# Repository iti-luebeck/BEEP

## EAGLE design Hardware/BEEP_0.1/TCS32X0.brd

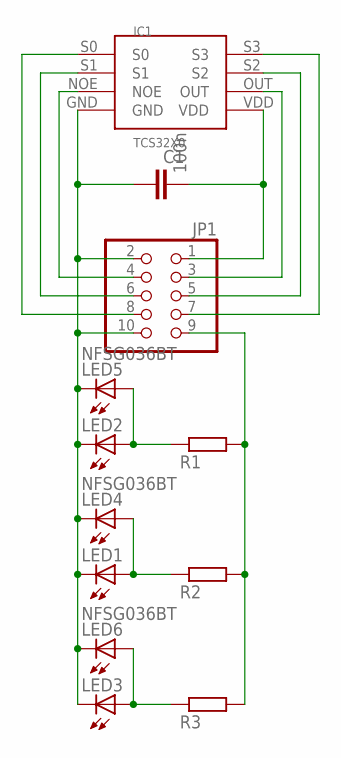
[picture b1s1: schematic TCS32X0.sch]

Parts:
C1: 100n; C0805
IC1: TCS32X0
JP1: PINHD-2X5; 2X05
LED1, LED2, LED3: LED3MM
LED4, LED5, LED6: NFSG036BT
R1, R2, R3: R-EU_M0805; M0805

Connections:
GND: C1.1, IC1.GND, JP1.2, JP1.10, LED1.K (C), LED2.K (C), LED3.K (C), LED4.C, LED5.C, LED6.C
unnamed: JP1.9, R1.2, R2.2, R3.2
unnamed: IC1.NOE, JP1.4
unnamed: IC1.S1, JP1.6
unnamed: C1.2, IC1.VDD, JP1.1
unnamed: IC1.OUT, JP1.3
unnamed: IC1.S2, JP1.5
unnamed: LED2.A, LED5.A, R1.1
unnamed: LED1.A, LED4.A, R2.1
unnamed: LED3.A, LED6.A, R3.1
unnamed: IC1.S0, JP1.8
unnamed: IC1.S3, JP1.7

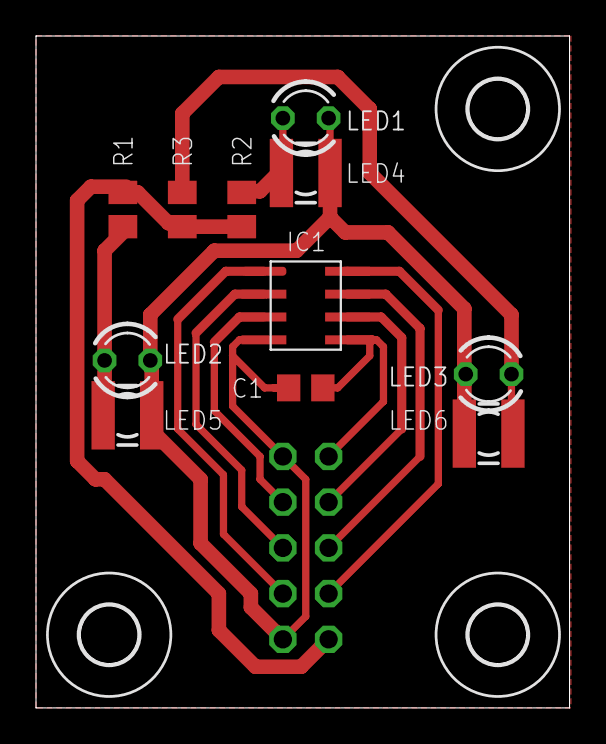
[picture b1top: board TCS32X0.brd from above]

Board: 2 copper layers, 29.6 x 37.3 mm, 15 parts (1 on the bottom side), 12 nets.

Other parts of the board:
U$2, U$3, U$4: 3,2

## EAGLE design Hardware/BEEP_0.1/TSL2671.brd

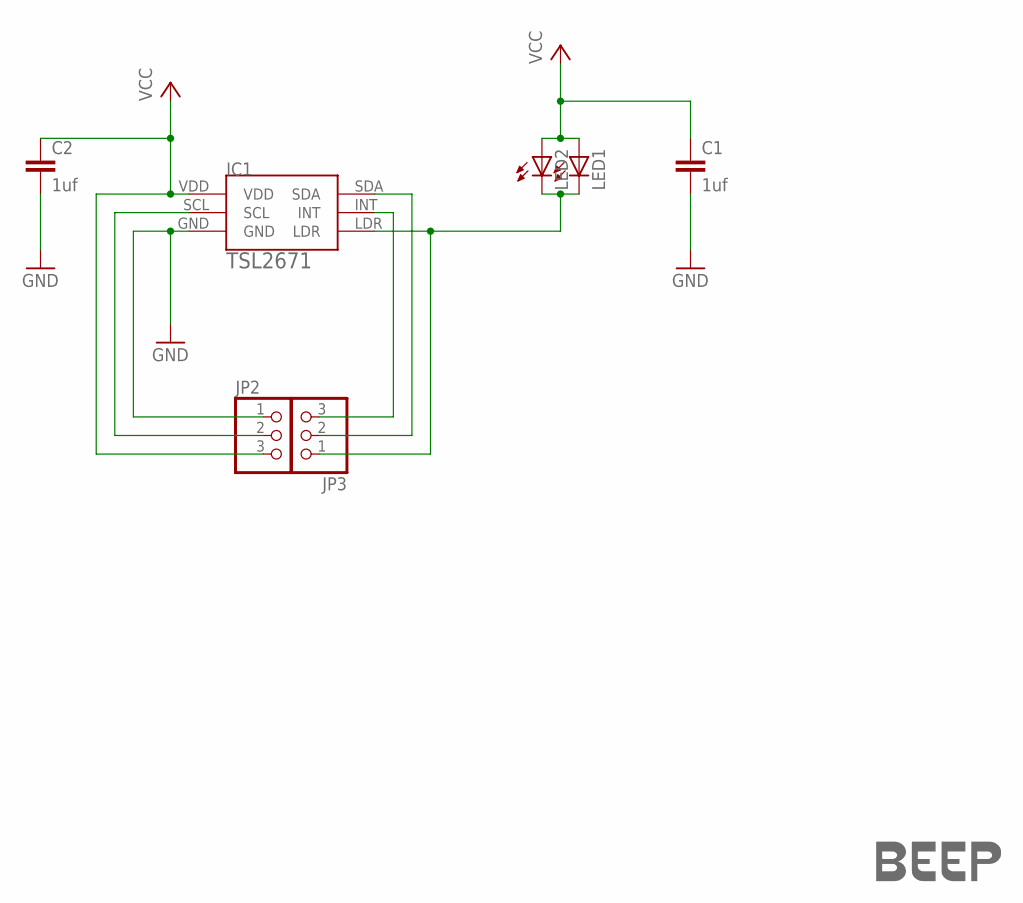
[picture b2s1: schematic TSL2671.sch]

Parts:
C1: 1uf; C025-025X050
C2: 1uf; C0805K
IC1: TSL2671
JP2, JP3: PINHD-1X3; 1X03
LED1: LED5MM
LED2: LEDCHIP-LED0805; CHIP-LED0805
U$1: LOGO-COPPER4; COPPER4

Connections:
GND: C1.2, C2.2, IC1.GND, JP2.1
unnamed: IC1.LDR, JP3.1, LED1.K (C), LED2.C
unnamed: IC1.SCL, JP2.2
unnamed: IC1.SDA, JP3.2
unnamed: IC1.INT, JP3.3
VCC: C1.1, C2.1, IC1.VDD, JP2.3, LED1.A, LED2.A

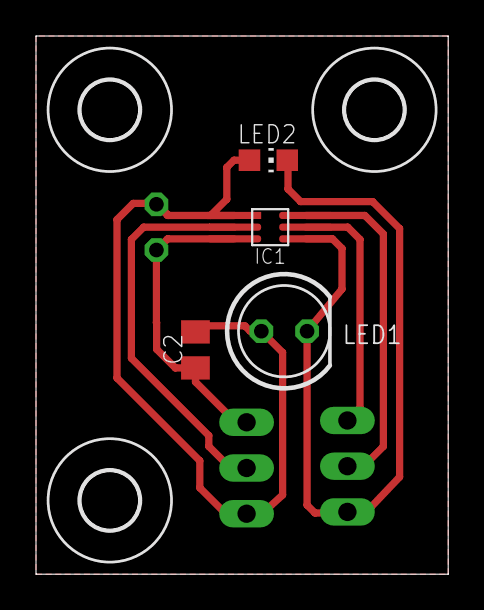
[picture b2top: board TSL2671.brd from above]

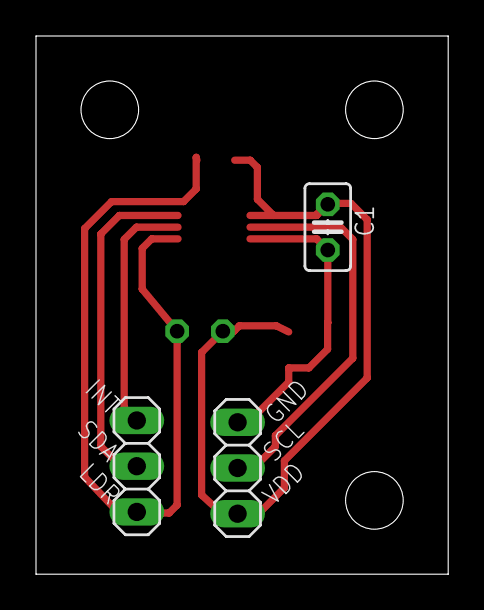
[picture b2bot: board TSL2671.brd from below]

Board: 2 copper layers, 22.9 x 29.9 mm, 11 parts (3 on the bottom side), 6 nets.

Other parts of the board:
U$2, U$3, U$4: 3,2

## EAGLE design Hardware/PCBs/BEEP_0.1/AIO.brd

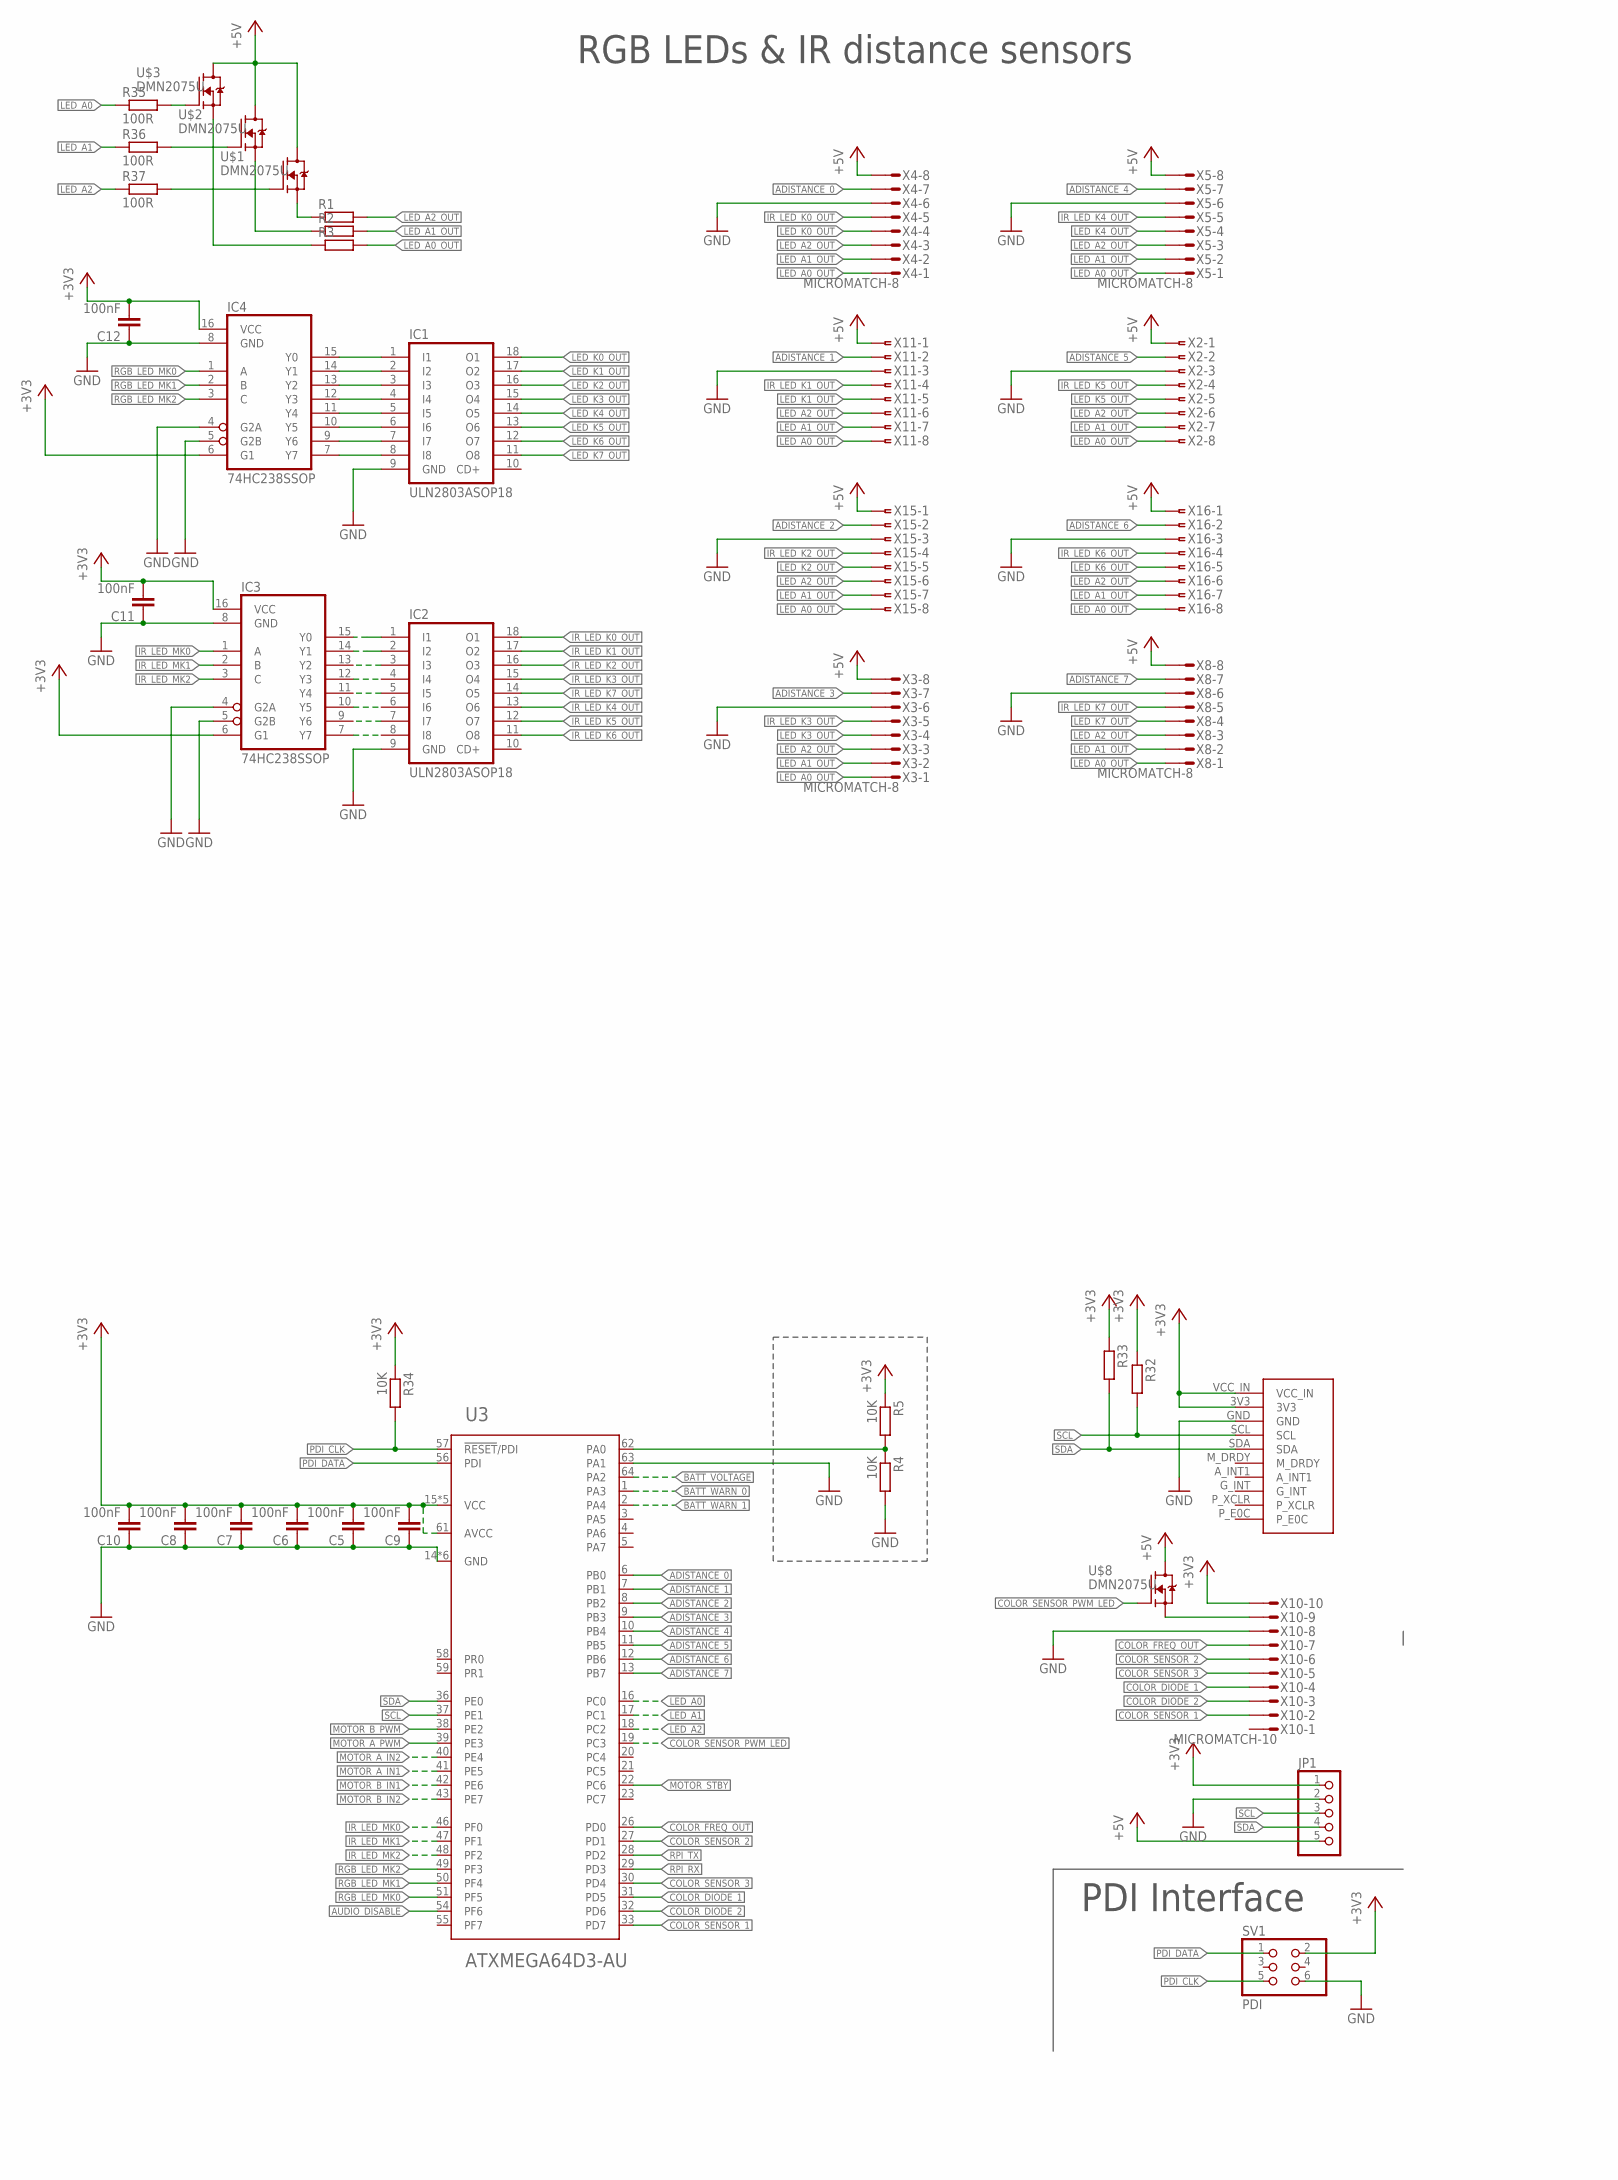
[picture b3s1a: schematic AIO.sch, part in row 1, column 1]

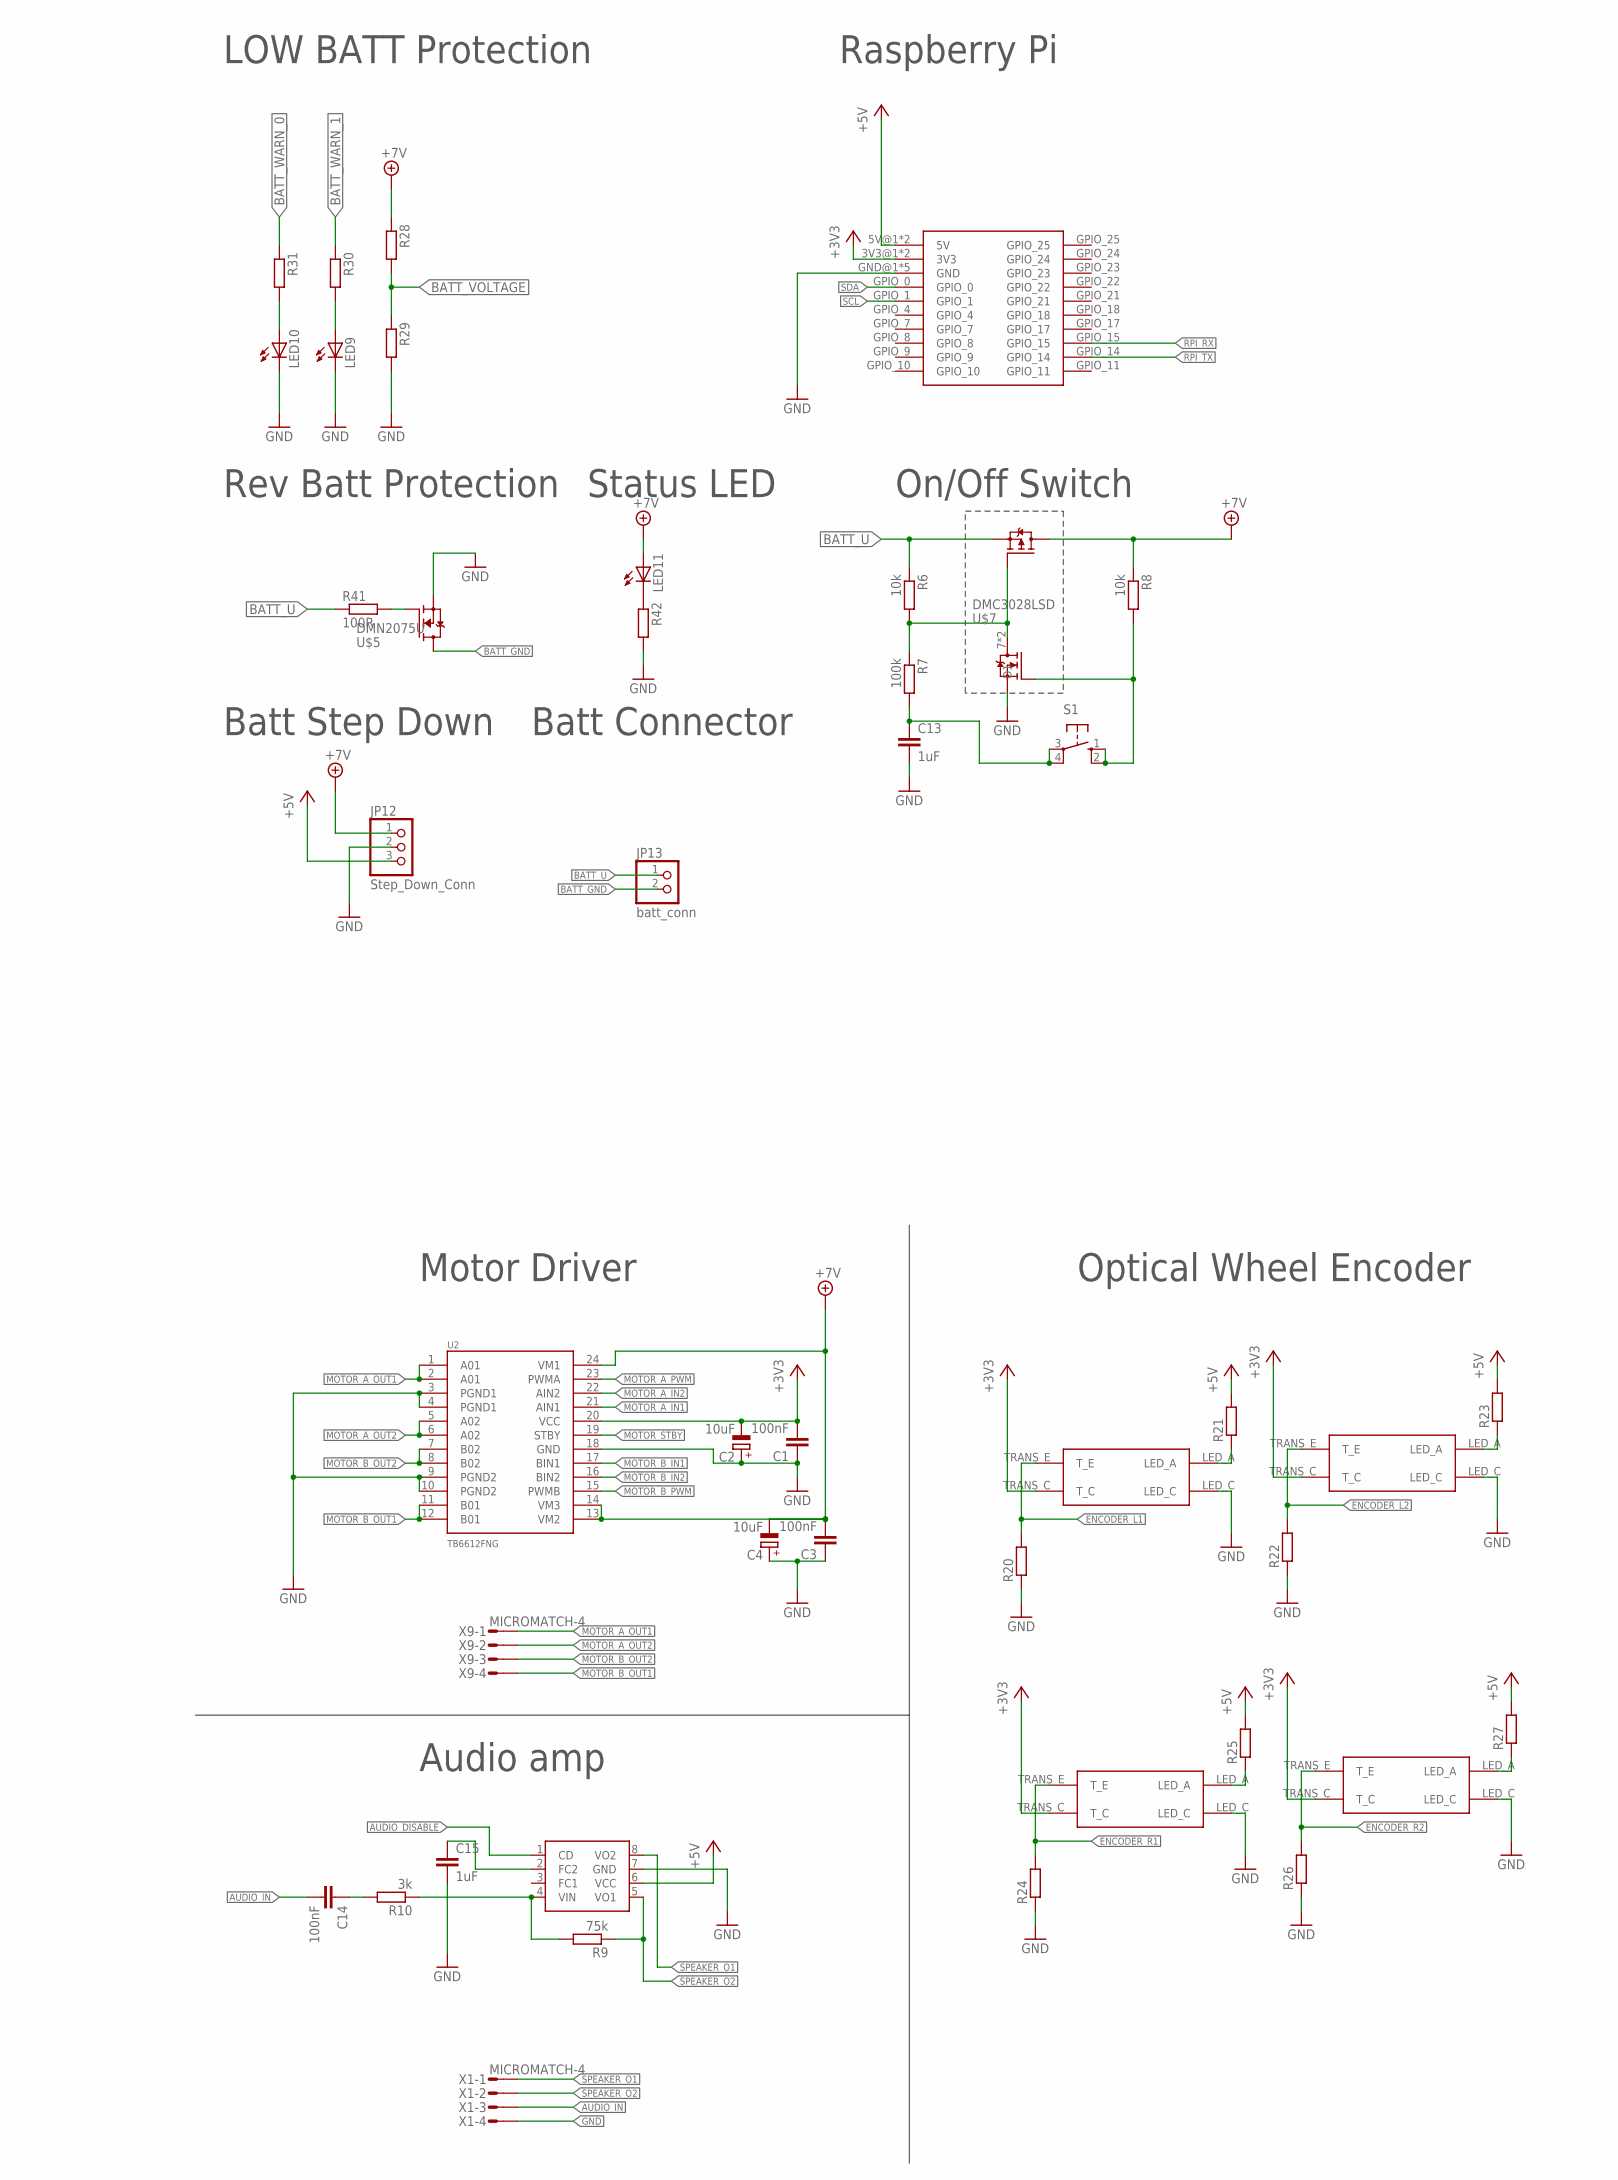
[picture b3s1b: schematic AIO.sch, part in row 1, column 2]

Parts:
C1, C3, C5, C6, C7, C8, C9, C10, C11, C12, C14: 100nF; C0603
C2, C4: 10uF; SMC_D
C13, C15: 1uF; C0603
IC1, IC2: ULN2803ASOP18; SOP18
IC3, IC4: 74HC238SSOP; SSOP16
IC5: TS34119SMD; SO08
JP1: PINHD-1X5; 1X05
JP12: Step_Down_Conn; 1X03
JP13: batt_conn; 1X02
LED9, LED10, LED11: LEDCHIPLED_0603; CHIPLED_0603
R1, R2, R3, R20, R21, R22, R23, R24, R25, R26, R27, R28, R29, R30, R31, R32, R33, R42: R-EU_R0603; R0603
R4, R5, R34: 10K; R0603
R6, R8: 10k; R0603
R7: 100k; R0603
R9: 75k; R0603
R10: 3k; R0603
R35, R36, R37, R41: 100R; R0603
S1: 10-XX; B3F-10XX
SV1: PDI; 2X03
U2: TB6612FNG; SSOP24
U3: ATXMEGA64D3-AU; TQFP-64A-64
U$1, U$2, U$3, U$5, U$8: DMN2075U; SOT95P240X112-3N
U$7: DMC3028LSD; SO08
U$21, U$22, U$23, U$24: CNY70
U$25: GY-81
U$26: RASPBERRY-PI; RASPERRRY-PI
X1, X9: MICROMATCH-4
X2, X11, X15, X16: FSIDE-8
X3, X4, X5, X8: MICROMATCH-8
X10: MICROMATCH-10

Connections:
+3V3: C1.2, C2.-, C5.2, C6.2, C7.2, C8.2, C9.2, C10.2, C11.2, C12.2, IC3.6 (G1), IC3.16 (VCC), IC4.6 (G1), IC4.16 (VCC), JP1.1, R5.1, R32.1, R33.1, R34.1, SV1.2, U2.20 (VCC), U3.15 (VCC), U3.25 (VCC), U3.35 (VCC), U3.45 (VCC), U3.53 (VCC), U3.61 (AVCC), U$21.TRANS_C (T_C), U$22.TRANS_C (T_C), U$23.TRANS_C (T_C), U$24.TRANS_C (T_C), U$25.3V3, U$25.VCC_IN, U$26.3V3@1 (3V3), U$26.3V3@2 (3V3), X10.10
+5V: IC5.6 (VCC), JP1.5, JP12.3, R21.2, R23.2, R25.2, R27.2, U$1.D, U$2.D, U$3.D, U$8.D, U$26.5V@1 (5V), U$26.5V@2 (5V), X2.1, X3.8, X4.8, X5.8, X8.8, X11.1, X15.1, X16.1
+7V: C3.2, C4.-, JP12.1, LED11.A, R8.1, R28.1, U2.13 (VM2), U2.14 (VM3), U2.24 (VM1), U$7.5 (D2), U$7.6 (D2)
ADISTANCE_0: U3.6 (PB0), X4.7
ADISTANCE_1: U3.7 (PB1), X11.2
ADISTANCE_2: U3.8 (PB2), X15.2
ADISTANCE_3: U3.9 (PB3), X3.7
ADISTANCE_4: U3.10 (PB4), X5.7
ADISTANCE_5: U3.11 (PB5), X2.2
ADISTANCE_6: U3.12 (PB6), X16.2
ADISTANCE_7: U3.13 (PB7), X8.7
AUDIO_DISABLE: IC5.1 (CD), U3.54 (PF6)
AUDIO_IN: C14.2, X1.3
BATT_GND: JP13.2, U$5.D
BATT_U: JP13.1, R6.1, R41.1, U$7.3 (S2)
BATT_VOLTAGE: R28.2, R29.1, U3.64 (PA2)
BATT_WARN_0: R31.1, U3.1 (PA3)
BATT_WARN_1: R30.1, U3.2 (PA4)
COLOR_DIODE_1: U3.31 (PD5), X10.4
COLOR_DIODE_2: U3.32 (PD6), X10.3
COLOR_FREQ_OUT: U3.26 (PD0), X10.7
COLOR_SENSOR_1: U3.33 (PD7), X10.2
COLOR_SENSOR_2: U3.27 (PD1), X10.6
COLOR_SENSOR_3: U3.30 (PD4), X10.5
COLOR_SENSOR_PWM_LED: U3.19 (PC3), U$8.G
ENCODER_L1: R20.2, U$21.TRANS_E (T_E)
ENCODER_L2: R22.2, U$22.TRANS_E (T_E)
ENCODER_R1: R24.2, U$23.TRANS_E (T_E)
ENCODER_R2: R26.2, U$24.TRANS_E (T_E)
GND: C1.1, C2.+, C3.1, C4.+, C5.1, C6.1, C7.1, C8.1, C9.1, C10.1, C11.1, C12.1, C13.2, C15.2, IC1.9 (GND), IC2.9 (GND), IC3.4 (G2A), IC3.5 (G2B), IC3.8 (GND), IC4.4 (G2A), IC4.5 (G2B), IC4.8 (GND), IC5.7 (GND), JP1.2, JP12.2, LED9.C, LED10.C, R4.2, R20.1, R22.1, R24.1, R26.1, R29.2, R42.2, SV1.6, U2.3 (PGND1), U2.4 (PGND1), U2.9 (PGND2), U2.10 (PGND2), U2.18 (GND), U3.14 (GND), U3.24 (GND), U3.34 (GND), U3.44 (GND), U3.52 (GND), U3.60 (GND), U3.63 (PA1), U$5.S, U$7.1 (S1), U$21.LED_C, U$22.LED_C, U$23.LED_C, U$24.LED_C, U$25.GND, U$26.GND@1 (GND), U$26.GND@2 (GND), U$26.GND@3 (GND), U$26.GND@4 (GND), U$26.GND@5 (GND), X1.4, X2.3, X3.6, X4.6, X5.6, X8.6, X10.8, X11.3, X15.3, X16.3
IR_LED_K0: IC2.1 (I1), IC3.15 (Y0)
IR_LED_K0_OUT: IC2.18 (O1), X4.5
IR_LED_K1: IC2.2 (I2), IC3.14 (Y1)
IR_LED_K1_OUT: IC2.17 (O2), X11.4
IR_LED_K2_OUT: IC2.16 (O3), X15.4
IR_LED_K3_OUT: IC2.15 (O4), X3.5
IR_LED_K4_OUT: IC2.13 (O6), X5.5
IR_LED_K5_OUT: IC2.12 (O7), X2.4
IR_LED_K6_OUT: IC2.11 (O8), X16.4
IR_LED_K7_OUT: IC2.14 (O5), X8.5
IR_LED_MK0: IC3.1 (A), U3.46 (PF0)
IR_LED_MK1: IC3.2 (B), U3.47 (PF1)
IR_LED_MK2: IC3.3 (C), U3.48 (PF2)
LED_A0: R35.1, U3.16 (PC0)
LED_A0_OUT: R3.2, X2.8, X3.1, X4.1, X5.1, X8.1, X11.8, X15.8, X16.8
LED_A1: R36.1, U3.17 (PC1)
LED_A1_OUT: R2.2, X2.7, X3.2, X4.2, X5.2, X8.2, X11.7, X15.7, X16.7
LED_A2: R37.1, U3.18 (PC2)
LED_A2_OUT: R1.2, X2.6, X3.3, X4.3, X5.3, X8.3, X11.6, X15.6, X16.6
LED_K0_OUT: IC1.18 (O1), X4.4
LED_K1_OUT: IC1.17 (O2), X11.5
LED_K2_OUT: IC1.16 (O3), X15.5
LED_K3_OUT: IC1.15 (O4), X3.4
LED_K4_OUT: IC1.14 (O5), X5.4
LED_K5_OUT: IC1.13 (O6), X2.5
LED_K6_OUT: IC1.12 (O7), X16.5
LED_K7_OUT: IC1.11 (O8), X8.4
MOTOR_A_IN1: U2.21 (AIN1), U3.41 (PE5)
MOTOR_A_IN2: U2.22 (AIN2), U3.40 (PE4)
MOTOR_A_OUT1: U2.1 (A01), U2.2 (A01), X9.1
MOTOR_A_OUT2: U2.5 (A02), U2.6 (A02), X9.2
MOTOR_A_PWM: U2.23 (PWMA), U3.39 (PE3)
MOTOR_B_IN1: U2.17 (BIN1), U3.42 (PE6)
MOTOR_B_IN2: U2.16 (BIN2), U3.43 (PE7)
MOTOR_B_OUT1: U2.11 (B01), U2.12 (B01), X9.4
MOTOR_B_OUT2: U2.7 (B02), U2.8 (B02), X9.3
MOTOR_B_PWM: U2.15 (PWMB), U3.38 (PE2)
MOTOR_STBY: U2.19 (STBY), U3.22 (PC6)
unnamed: R1.1, U$1.S
unnamed: R2.1, U$2.S
unnamed: R3.1, U$3.S
unnamed: R4.1, R5.2, U3.62 (PA0)
unnamed: U$8.S, X10.9
unnamed: IC2.3 (I3), IC3.13 (Y2)
unnamed: IC2.4 (I4), IC3.12 (Y3)
unnamed: R41.2, U$5.G
unnamed: IC2.5 (I5), IC3.11 (Y4)
unnamed: IC2.6 (I6), IC3.10 (Y5)
unnamed: R23.1, U$22.LED_A
unnamed: IC2.7 (I7), IC3.9 (Y6)
unnamed: IC2.8 (I8), IC3.7 (Y7)
unnamed: IC5.4 (VIN), R9.2, R10.1
unnamed: C13.1, R7.2, S1.3, S1.4 (P1)
unnamed: C14.1, R10.2
unnamed: R8.2, S1.1 (S), S1.2 (S1), U$7.2 (G1)
unnamed: LED11.C, R42.1
unnamed: R25.1, U$23.LED_A
unnamed: IC1.1 (I1), IC4.15 (Y0)
unnamed: R6.2, R7.1, U$7.4 (G2), U$7.7 (D1), U$7.8 (D1)
unnamed: R21.1, U$21.LED_A
unnamed: IC1.2 (I2), IC4.14 (Y1)
unnamed: R27.1, U$24.LED_A
unnamed: IC1.3 (I3), IC4.13 (Y2)
unnamed: IC1.4 (I4), IC4.12 (Y3)
unnamed: LED9.A, R30.2
unnamed: IC1.5 (I5), IC4.11 (Y4)
unnamed: IC1.6 (I6), IC4.10 (Y5)
unnamed: LED10.A, R31.2
unnamed: IC1.7 (I7), IC4.9 (Y6)
unnamed: IC1.8 (I8), IC4.7 (Y7)
unnamed: C15.1, IC5.2 (FC2)
unnamed: R35.2, U$3.G
unnamed: R36.2, U$2.G
unnamed: R37.2, U$1.G
PDI_CLK: R34.2, SV1.5, U3.57 (!RESET!/PDI)
PDI_DATA: SV1.1, U3.56 (PDI)
RGB_LED_MK0: IC4.1 (A), U3.51 (PF5)
RGB_LED_MK1: IC4.2 (B), U3.50 (PF4)
RGB_LED_MK2: IC4.3 (C), U3.49 (PF3)
RPI_RX: U3.29 (PD3), U$26.GPIO_15
RPI_TX: U3.28 (PD2), U$26.GPIO_14
SCL: JP1.3, R32.2, U3.37 (PE1), U$25.SCL, U$26.GPIO_1
SDA: JP1.4, R33.2, U3.36 (PE0), U$25.SDA, U$26.GPIO_0
SPEAKER_O1: IC5.8 (VO2), X1.1
SPEAKER_O2: IC5.5 (VO1), R9.1, X1.2

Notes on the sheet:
Motor Driver
Optical Wheel Encoder
RGB LEDs & IR distance sensors
PDI Interface
Rev Batt Protection
LOW BATT Protection
Raspberry Pi
Batt Step Down
Batt Connector
On/Off Switch
Status LED
Audio amp

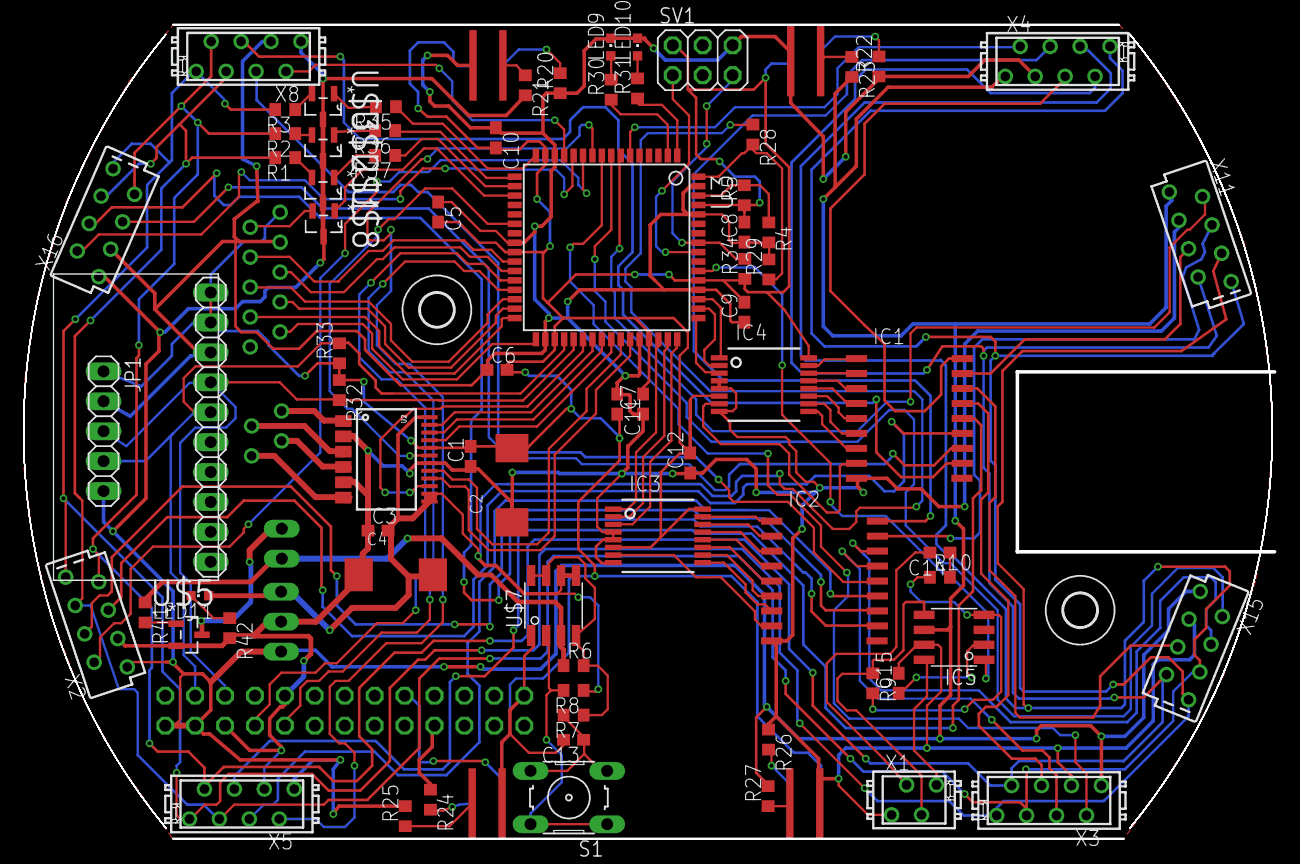
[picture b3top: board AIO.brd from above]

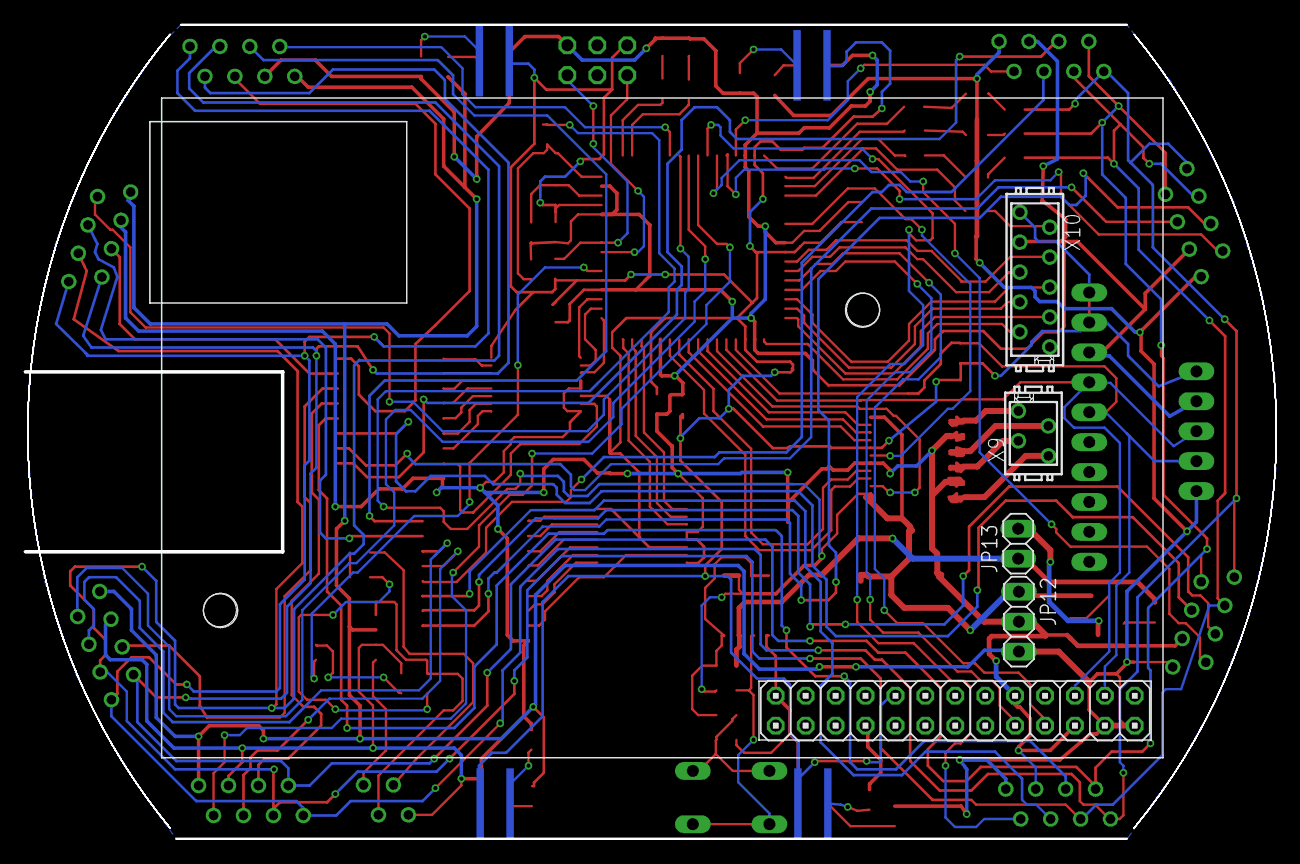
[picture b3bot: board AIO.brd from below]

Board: 4 copper layers, 106.2 x 69.1 mm, 85 parts (5 on the bottom side), 115 nets.

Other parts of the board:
U$4, U$6: 2,8

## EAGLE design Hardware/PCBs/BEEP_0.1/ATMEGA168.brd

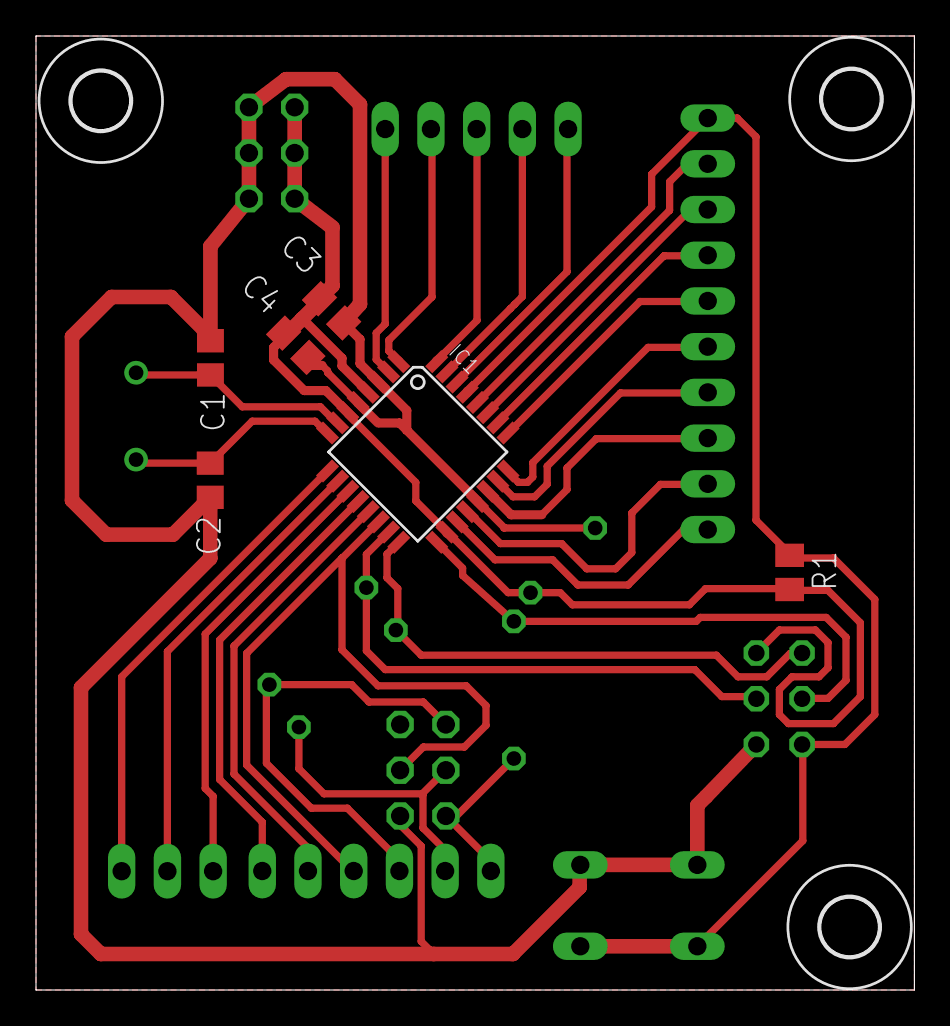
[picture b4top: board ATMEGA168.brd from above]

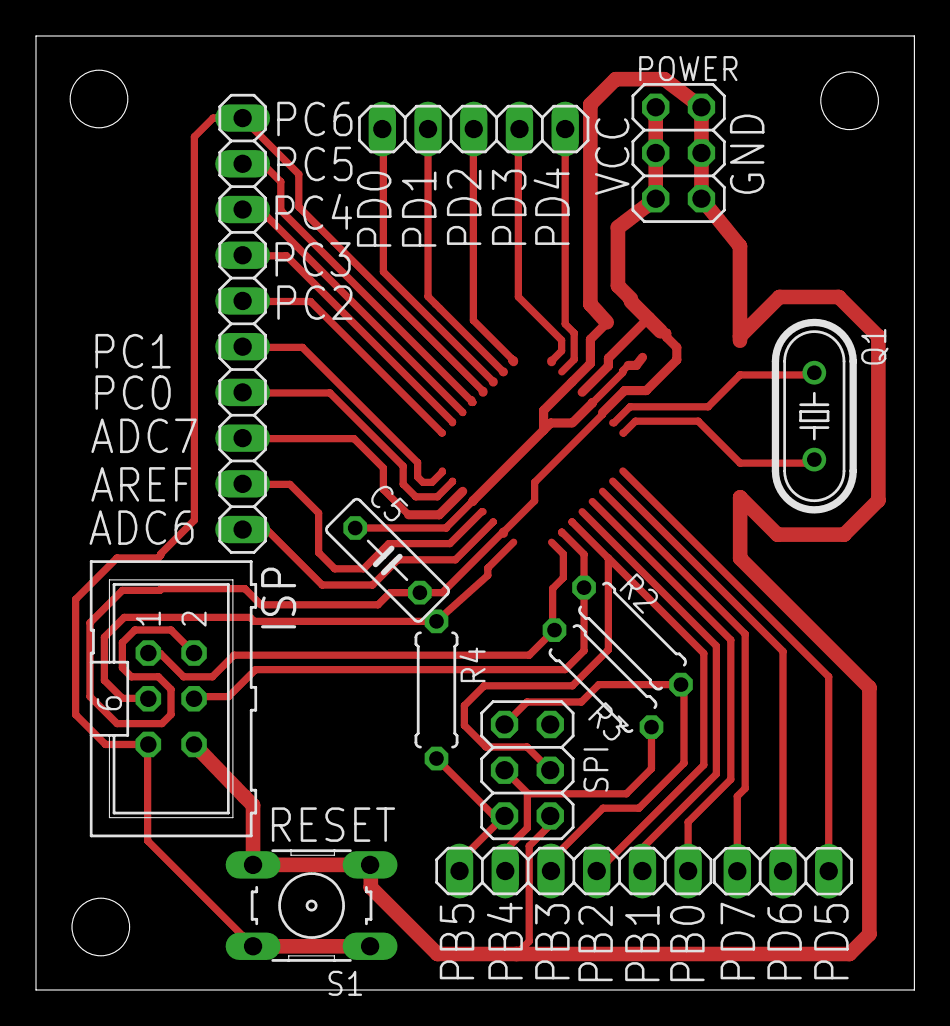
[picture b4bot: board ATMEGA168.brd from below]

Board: 2 copper layers, 48.8 x 53.0 mm, 23 parts (13 on the bottom side), 31 nets.

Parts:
C1, C2: C0805
C3, C4: 100n; C0805
C5: 100n; C050-025X075
H1, H2, H3: 3,2
IC1: ATMEGA48/88/168-AU; TQFP32-08
ISP: ML6
JP2: 1X10
JP3: 1X05
JP4: 1X06
JP5: 1X03
POWER: 2X03
Q1: 20Mhz; HC49/S
R1: 10k; M0805
R2, R3, R4: 1k; 0207/7
S1: B3F-10XX
SPI: 2X03
U$1: LOGO-COPPER4; COPPER4

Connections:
AREF: IC1.20, JP2.2
GND: C1.1, C2.1, C3.1, C4.1, C5.1, IC1.3, IC1.5, IC1.21, ISP.6, POWER.2, POWER.4, POWER.6, S1.3, S1.4, SPI.6
MISO: IC1.16, ISP.1, R3.1
MOSI: IC1.15, ISP.4, R2.1
unnamed: C1.2, IC1.7, Q1.1
unnamed: C2.2, IC1.8, Q1.2
unnamed: IC1.28, JP2.9
unnamed: IC1.27, JP2.8
unnamed: IC1.26, JP2.7
unnamed: IC1.25, JP2.6
unnamed: IC1.9, JP5.1
unnamed: IC1.10, JP5.2
unnamed: IC1.30, JP3.1
unnamed: IC1.31, JP3.2
unnamed: IC1.32, JP3.3
unnamed: IC1.1, JP3.4
unnamed: IC1.2, JP3.5
unnamed: IC1.11, JP5.3
unnamed: IC1.24, JP2.5
unnamed: IC1.23, JP2.4
unnamed: IC1.12, JP4.1
unnamed: IC1.13, JP4.2
unnamed: IC1.19, JP2.1
unnamed: IC1.22, JP2.3
RST: IC1.29, ISP.5, JP2.10, R1.1, S1.1, S1.2
SCK: IC1.17, ISP.3, R4.1
SCLK: JP4.6, R4.2, SPI.5
SIN: JP4.4, R2.2, SPI.1
SOUT: JP4.5, R3.2, SPI.3
SS: IC1.14, JP4.3, SPI.4
VCC: C3.2, C4.2, C5.2, IC1.4, IC1.6, IC1.18, ISP.2, POWER.1, POWER.3, POWER.5, R1.2

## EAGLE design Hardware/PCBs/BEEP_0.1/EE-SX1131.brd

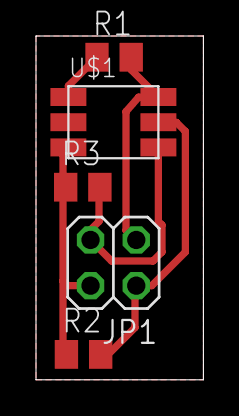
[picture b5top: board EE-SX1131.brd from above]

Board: 2 copper layers, 9.3 x 19.1 mm, 5 parts (0 on the bottom side), 5 nets.

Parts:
JP1: 2X02
R1: 220R; M0805
R2, R3: 20k; M0805
U$1: EE-SX1131

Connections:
GND: JP1.4, R2.1, R3.1, U$1.K
unnamed: R1.1, U$1.A
unnamed: JP1.3, R3.2, U$1.E2
unnamed: JP1.2, R2.2, U$1.E1
VCC: JP1.1, R1.2, U$1.C

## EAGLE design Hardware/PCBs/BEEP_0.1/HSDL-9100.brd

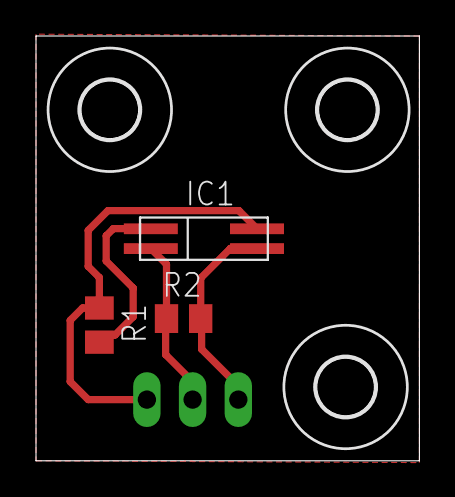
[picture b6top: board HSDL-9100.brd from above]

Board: 2 copper layers, 21.3 x 23.6 mm, 8 parts (1 on the bottom side), 4 nets.

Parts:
IC1: HSDL-9100
JP1: 1X03
R1, R2: M0805
U$1: LOGO-COPPER3; COPPER3
U$2, U$3, U$4: 3,2

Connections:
ADATA: IC1.DET_A, JP1.3, R2.2
GND: IC1.LED_K, JP1.2, R2.1
unnamed: IC1.LED_A, R1.2
VCC: IC1.DET_K, JP1.1, R1.1

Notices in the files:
parts and their libraries:
SparkFun-PowerIC: Licensing: CC v3.0 Share-Alike You are welcome to use this library for commercial purposes.
